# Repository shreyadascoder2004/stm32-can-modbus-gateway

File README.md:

# STM32 CAN–Modbus Industrial Gateway

A 4-layer STM32-based industrial protocol gateway that bridges RS-485/Modbus-RTU
networks with CAN bus networks — designed end-to-end from schematic to PCB layout
in KiCad, with C firmware handling real-time protocol translation.

## Why this exists

Industrial factory floors often run a mix of legacy RS-485/Modbus-RTU equipment
(sensors, PLCs, HMIs) and newer CAN-based nodes (motor controllers, automotive-grade
modules). This gateway lets a Modbus master (PC, PLC, SCADA system) read and write
values on CAN-based devices without either side needing to natively support the
other's protocol — the same role commercial gateways (e.g. Moxa, Advantech) fill
in real deployments.

## How it works

1. A Modbus master sends a request (Read Holding Registers / Write Single Register)
   over RS-485
2. The STM32 receives it via UART, validates the frame (CRC16), and parses the
   register address and value
3. A lookup table maps the Modbus register to a CAN ID
4. The STM32 sends the corresponding CAN frame onto the bus
5. A CAN node responds; the STM32 receives it, maps it back to a Modbus register,
   and replies to the master over RS-485

USB is reserved for local configuration/debug access.

## Hardware

- **MCU**: STM32F407VET6 (LQFP100)
- **Power**: 24V DC input → TPS54233 buck (5V) → AP1117-33 LDO (3.3V)
- **RS-485**: MAX485E transceiver, jumper-selectable termination, fail-safe biasing
- **CAN**: SN65HVD230 transceiver, jumper-selectable 120Ω termination
- **Board**: 4-layer stackup (Signal / GND plane / 3V3 plane / Signal), designed
  in KiCad — schematic, footprint assignment, and layout completed with dedicated
  ground and power planes

See `/hardware` for the full KiCad project.

## Firmware

Written in C using the STM32 HAL, structured so the protocol logic is
hardware-independent and separately testable:

- `modbus_crc.c` — Modbus CRC16 checksum
- `modbus_parser.c` — Modbus RTU frame parsing and response building
- `can_mapping.c` — Modbus register ↔ CAN ID lookup table
- `main.c` — HAL integration: UART receive interrupt, CAN filter/notification
  setup, and the gateway's main translation loop

Clock tree: 8MHz HSE crystal → PLL → 168MHz SYSCLK, with CAN bus timing configured
for 500kbps on the 42MHz APB1 peripheral clock.

See `/firmware` for the full STM32CubeIDE project.

## Status

- Schematic: complete, ERC-clean
- PCB layout: components placed, 4-layer stackup and plane pours complete,
  routing in progress
- Firmware: compiles cleanly against the current pin mapping; logic modules
  (CRC, frame parsing, ID mapping) are hardware-independent and unit-testable
  on a PC
- Hardware validation: pending PCB fabrication and assembly — no physical
  board has been tested yet

## Build instructions

**Hardware**: open `hardware/*.kicad_pro` in KiCad 8+

**Firmware**: open `firmware/` as an existing project in STM32CubeIDE,
or import via *File → Open Projects from File System*

## License

MIT

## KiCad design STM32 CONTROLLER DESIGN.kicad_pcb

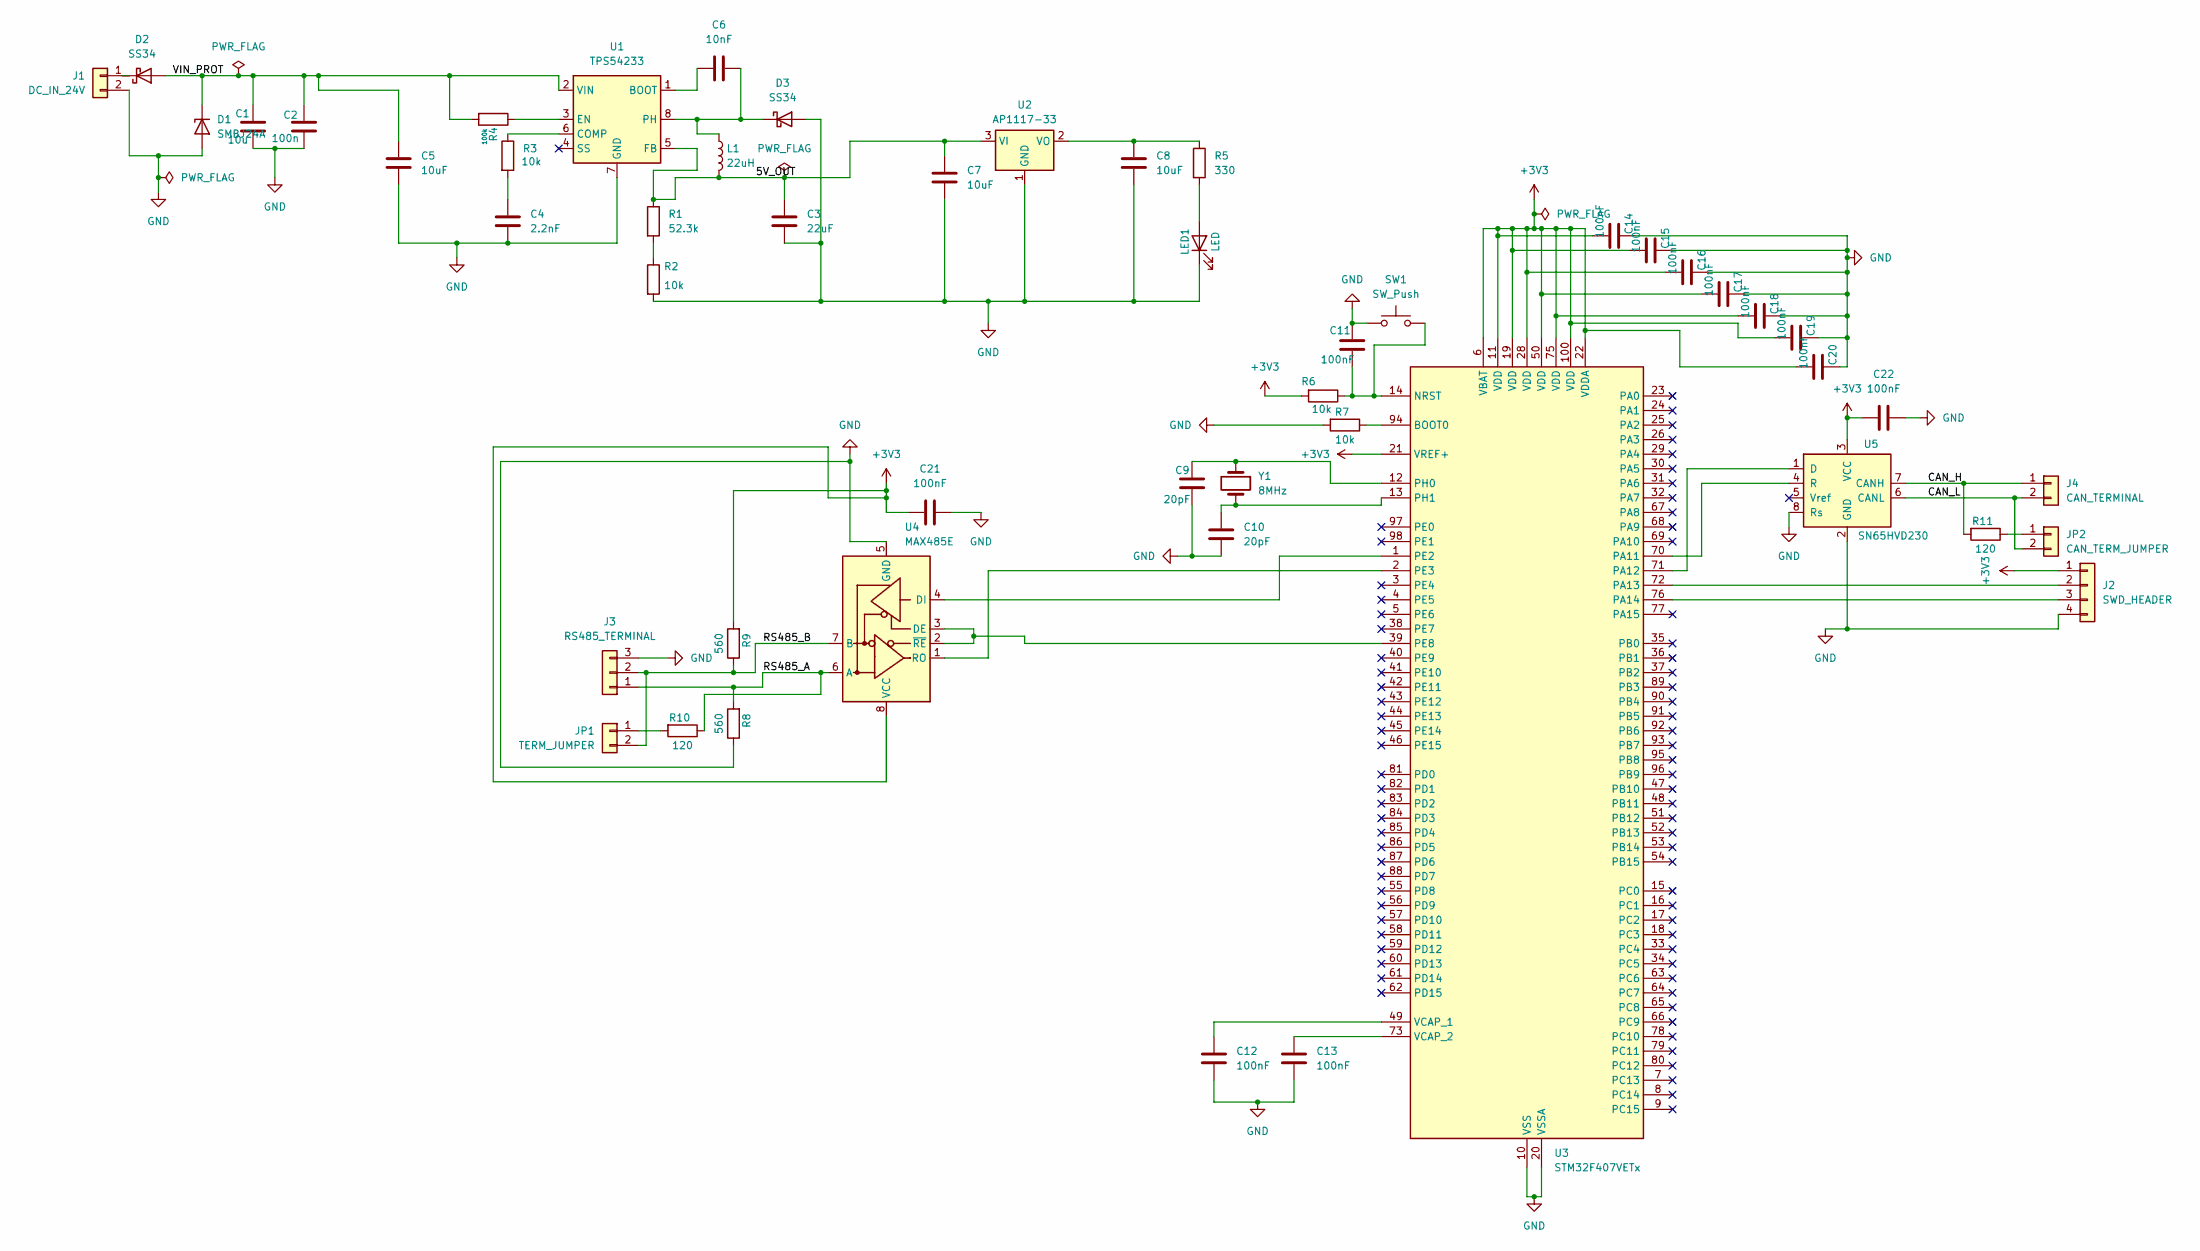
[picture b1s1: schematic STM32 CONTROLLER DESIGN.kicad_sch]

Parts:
C1: 10u; C_0805_2012Metric
C2: 100n; C_0805_2012Metric
C3: 22uF; C_0805_2012Metric
C4: 2.2nF; C_0805_2012Metric
C5, C7, C8: 10uF; C_0805_2012Metric
C6: 10nF; C_0805_2012Metric
C9, C10: 20pF; C_0805_2012Metric
C11, C12, C13, C14, C15, C16, C17, C18, C19, C20, C21, C22: 100nF; C_0805_2012Metric
D1: SMBJ24A; D_SMB
D2, D3: SS34; D_SMA
J1: DC_IN_24V; TerminalBlock_Phoenix_MKDS-1,5-2-5.08_1x02_P5.08mm_Horizont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
J2: SWD_HEADER; PinHeader_1x04_P2.54mm_Vertical
J3: RS485_TERMINAL; TerminalBlock_Phoenix_MKDS-1,5-3_1x03_P5.00mm_Horizontal
J4: CAN_TERMINAL; TerminalBlock_Phoenix_MKDS-1,5-2-5.08_1x02_P5.08mm_Horizont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
JP1: TERM_JUMPER; PinHeader_1x02_P2.54mm_Vertical
JP2: CAN_TERM_JUMPER; PinHeader_1x02_P2.54mm_Vertical
L1: 22uH; L_1210_3225Metric
LED1: LED; LED_0805_2012Metric
R1: 52.3k; R_0805_2012Metric
R2, R3, R6, R7: 10k; R_0805_2012Metric
R4: 100k; R_0805_2012Metric
R5: 330; R_0805_2012Metric
R8, R9: 560; R_0805_2012Metric
R10, R11: 120; R_0805_2012Metric
SW1: SW_Push; SW_SPST_TL3305A
U1: TPS54233; SOIC-8_3.9x4.9mm_P1.27mm
U2: AP1117-33; SOT-223-3_TabPin2
U3: STM32F407VETx; LQFP-100_14x14mm_P0.5mm
U4: MAX485E; SOIC-8_3.9x4.9mm_P1.27mm
U5: SN65HVD230; SOIC-8_3.9x4.9mm_P1.27mm
Y1: 8MHz; Crystal_SMD_3225-4Pin_3.2x2.5mm

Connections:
+3V3: C14.2, C15.2, C16.2, C17.2, C18.2, C19.2, C20.2, C21.2, C22.2, J2.1, R6.2, R9.2, U3.6 (VBAT), U3.11 (VDD), U3.19 (VDD), U3.21 (VREF+), U3.22 (VDDA), U3.28 (VDD), U3.50 (VDD), U3.75 (VDD), U3.100 (VDD), U4.8 (VCC), U5.3 (VCC)
/5V_OUT: C3.1, C7.1, L1.2, R1.1, U1.5 (FB), U2.3 (VI)
/CAN_H: J4.1, R11.2, U5.7 (CANH)
/CAN_L: J4.2, JP2.2, U5.6 (CANL)
/RS485_A: J3.1, R8.2, R10.1, U4.6 (A)
/RS485_B: J3.2, JP1.2, R9.1, U4.7 (B)
/VIN_PROT: C1.1, C2.1, C5.1, D1.1 (K), D2.2 (A), R4.2, U1.2 (VIN)
GND: C1.2, C2.2, C3.2, C4.2, C5.2, C7.2, C8.2, C9.2, C10.2, C11.1, C12.2, C13.2, C14.1, C15.1, C16.1, C17.1, C18.1, C19.1, C20.1, C21.1, C22.1, D1.2 (A), D3.2 (A), J1.2, J2.4, J3.3, LED1.1 (K), R2.2, R7.2, R8.1, SW1.1, U1.7 (GND), U2.1 (GND), U3.10 (VSS), U3.20 (VSSA), U3.27 (VSS), U3.74 (VSS), U3.99 (VSS), U4.5 (GND), U5.2 (GND), U5.8 (Rs)
unnamed: C4.1, R3.2
unnamed: D2.1 (K), J1.1
unnamed: C6.1, D3.1 (K), L1.1, U1.8 (PH)
unnamed: J2.2, U3.72 (PA13)
unnamed: J2.3, U3.76 (PA14)
unnamed: JP1.1, R10.2
unnamed: JP2.1, R11.1
unnamed: LED1.2 (A), R5.2
unnamed: R1.2, R2.1
unnamed: C6.2, U1.1 (BOOT)
unnamed: R3.1, U1.6 (COMP)
unnamed: R4.1, U1.3 (EN)
unnamed: C8.1, R5.1, U2.2 (VO)
unnamed: R7.1, U3.94 (BOOT0)
unnamed: C11.2, R6.1, SW1.2, U3.14 (NRST)
unnamed: U3.70 (PA11), U5.4 (R)
unnamed: U3.71 (PA12), U5.1 (D)
unnamed: U3.1 (PE2), U4.4 (DI)
unnamed: U3.2 (PE3), U4.1 (RO)
unnamed: U3.39 (PE8), U4.2 (~RE), U4.3 (DE)
unnamed: C9.1, U3.12 (PH0), Y1.1
unnamed: C10.1, U3.13 (PH1), Y1.2
unnamed: C12.1, U3.49 (VCAP_1)
unnamed: C13.1, U3.73 (VCAP_2)

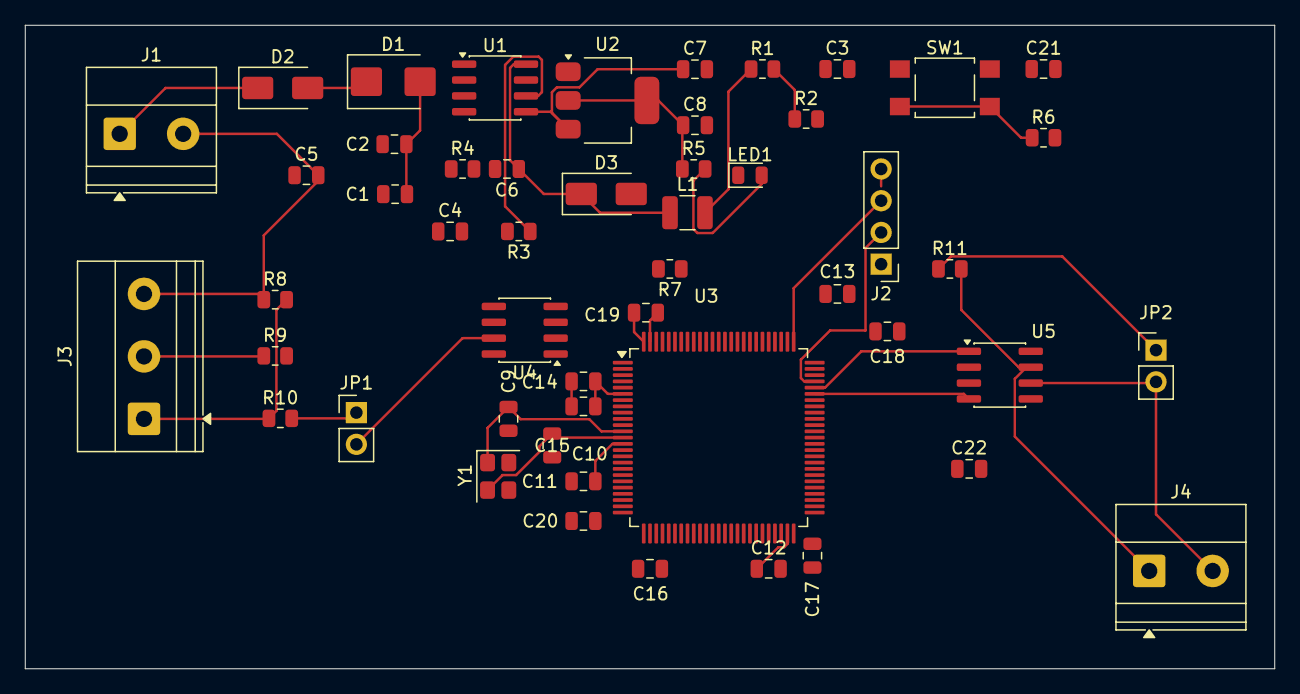
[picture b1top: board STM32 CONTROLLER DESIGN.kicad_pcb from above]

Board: 4 copper layers, 100.0 x 51.5 mm, 51 parts (0 on the bottom side), 32 nets.
